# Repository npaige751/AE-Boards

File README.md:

Circuit board designs for acoustic imager.

Central hub board with an FPGA, connecting to four large boards surrounding it that hold the microphone array.

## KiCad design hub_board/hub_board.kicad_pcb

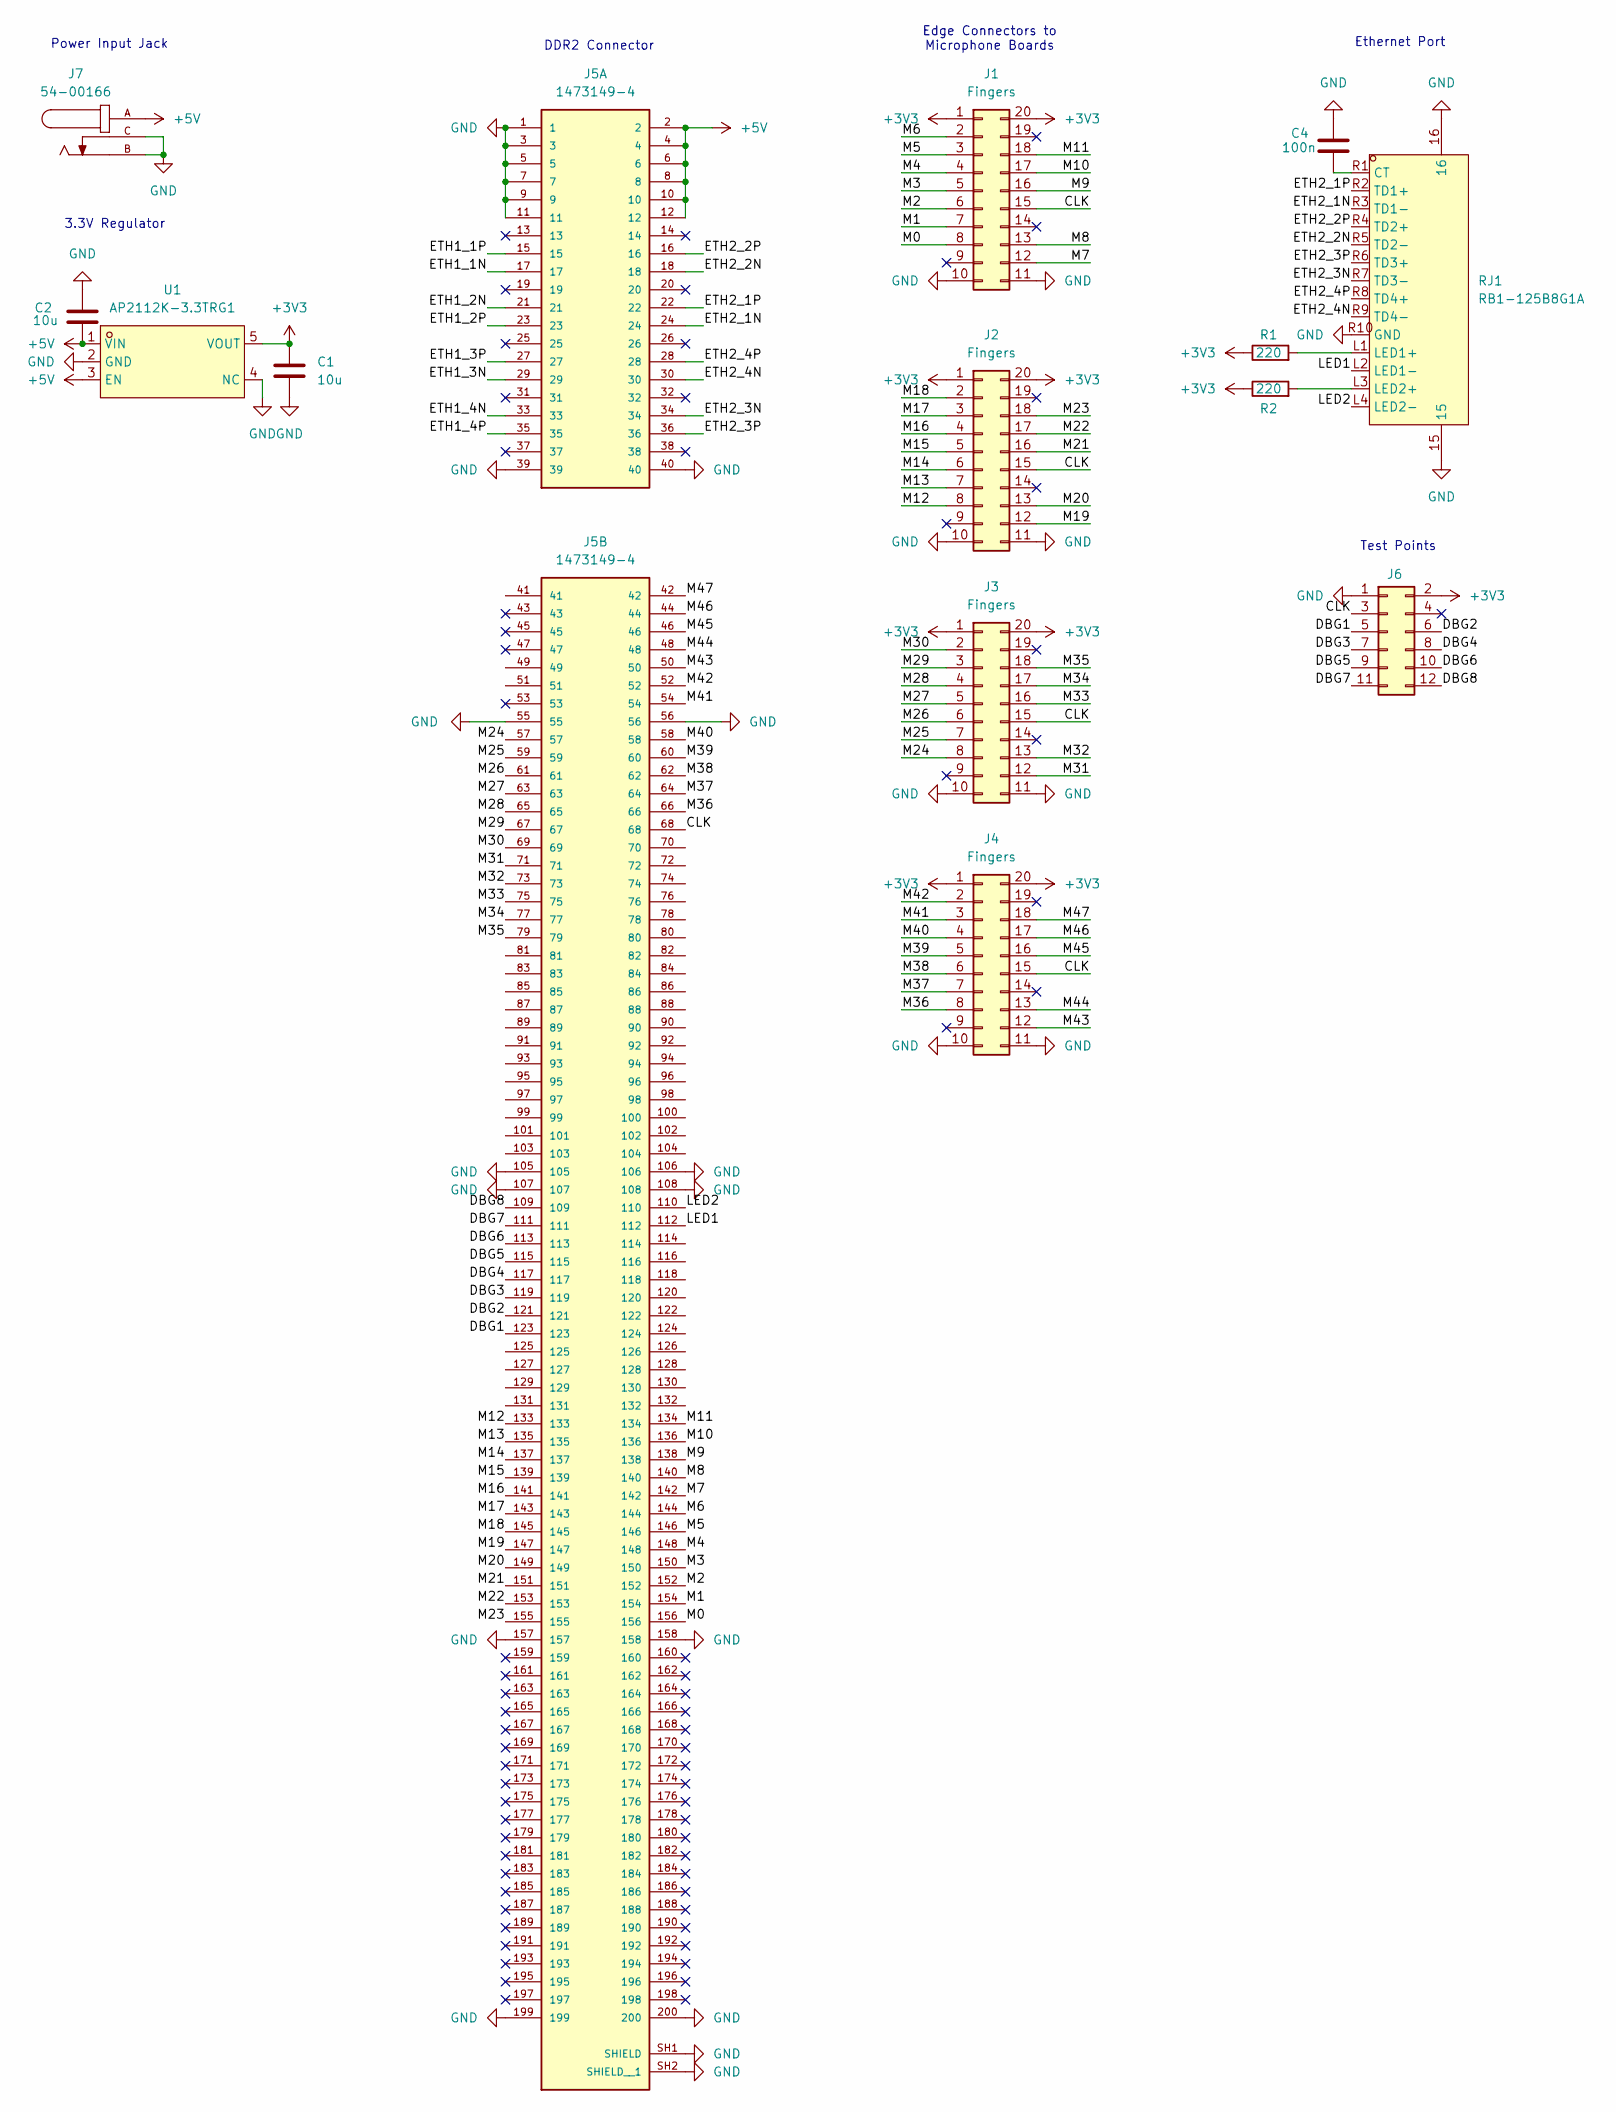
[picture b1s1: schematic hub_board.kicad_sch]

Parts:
C1, C2: 10u
C4: 100n
J1, J2, J3, J4: Fingers
J5: 1473149-4; TE_1473149-4
J6: Test Points
J7: 54-00166; TENSILITY_54-00166; PARTREV A
R1, R2: 220
RJ1: RB1-125B8G1A; RJ45-TH_RB1-125B8G1A; LCSC Part C363353
U1: AP2112K-3.3TRG1; SOT-25-5_L2.9-W1.6-P0.95-LS2.8-BL; LCSC Part C51118

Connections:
+3V3: C1.1, J1.1, J1.20, J2.1, J2.20, J3.1, J3.20, J4.1, J4.20, J6.2, R1.1, R2.1, U1.5 (VOUT)
+5V: C2.2, J5.2, J5.4, J5.6, J5.8, J5.10, J5.12, J7.A, U1.1 (VIN), U1.3 (EN)
/CLK: J1.15, J2.15, J3.15, J4.15, J5.68, J6.3
/DBG1: J5.123, J6.5
/DBG2: J5.121, J6.6
/DBG3: J5.119, J6.7
/DBG4: J5.117, J6.8
/DBG5: J5.115, J6.9
/DBG6: J5.113, J6.10
/DBG7: J5.111, J6.11
/DBG8: J5.109, J6.12
/ETH1_1N: J5.17
/ETH1_1P: J5.15
/ETH1_2N: J5.21
/ETH1_2P: J5.23
/ETH1_3N: J5.29
/ETH1_3P: J5.27
/ETH1_4N: J5.33
/ETH1_4P: J5.35
/ETH2_1N: J5.24, RJ1.R3 (TD1-)
/ETH2_1P: J5.22, RJ1.R2 (TD1+)
/ETH2_2N: J5.18, RJ1.R5 (TD2-)
/ETH2_2P: J5.16, RJ1.R4 (TD2+)
/ETH2_3N: J5.34, RJ1.R7 (TD3-)
/ETH2_3P: J5.36, RJ1.R6 (TD3+)
/ETH2_4N: J5.30, RJ1.R9 (TD4-)
/ETH2_4P: J5.28, RJ1.R8 (TD4+)
/LED1: J5.112, RJ1.L2 (LED1-)
/LED2: J5.110, RJ1.L4 (LED2-)
/M0: J1.8, J5.156
/M1: J1.7, J5.154
/M2: J1.6, J5.152
/M3: J1.5, J5.150
/M4: J1.4, J5.148
/M5: J1.3, J5.146
/M6: J1.2, J5.144
/M7: J1.12, J5.142
/M8: J1.13, J5.140
/M9: J1.16, J5.138
/M10: J1.17, J5.136
/M11: J1.18, J5.134
/M12: J2.8, J5.133
/M13: J2.7, J5.135
/M14: J2.6, J5.137
/M15: J2.5, J5.139
/M16: J2.4, J5.141
/M17: J2.3, J5.143
/M18: J2.2, J5.145
/M19: J2.12, J5.147
/M20: J2.13, J5.149
/M21: J2.16, J5.151
/M22: J2.17, J5.153
/M23: J2.18, J5.155
/M24: J3.8, J5.57
/M25: J3.7, J5.59
/M26: J3.6, J5.61
/M27: J3.5, J5.63
/M28: J3.4, J5.65
/M29: J3.3, J5.67
/M30: J3.2, J5.69
/M31: J3.12, J5.71
/M32: J3.13, J5.73
/M33: J3.16, J5.75
/M34: J3.17, J5.77
/M35: J3.18, J5.79
/M36: J4.8, J5.66
/M37: J4.7, J5.64
/M38: J4.6, J5.62
/M39: J4.5, J5.60
/M40: J4.4, J5.58
/M41: J4.3, J5.54
/M42: J4.2, J5.52
/M43: J4.12, J5.50
/M44: J4.13, J5.48
/M45: J4.16, J5.46
/M46: J4.17, J5.44
/M47: J4.18, J5.42
GND: C1.2, C2.1, C4.2, J1.10, J1.11, J2.10, J2.11, J3.10, J3.11, J4.10, J4.11, J5.1, J5.3, J5.5, J5.7, J5.9, J5.11, J5.39, J5.40, J5.55, J5.56, J5.105, J5.106, J5.107, J5.108, J5.157, J5.158, J5.199, J5.200, J5.SH1 (SHIELD), J5.SH2 (SHIELD__1), J6.1, J7.B, J7.C, RJ1.15, RJ1.16, RJ1.R10 (GND), U1.2 (GND), U1.4 (NC)
unnamed: C4.1, RJ1.R1 (CT)
unnamed: R1.2, RJ1.L1 (LED1+)
unnamed: R2.2, RJ1.L3 (LED2+)

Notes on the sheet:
3.3V Regulator
Power Input Jack
DDR2 Connector
Ethernet Port
Test Points
Edge Connectors to Microphone Boards

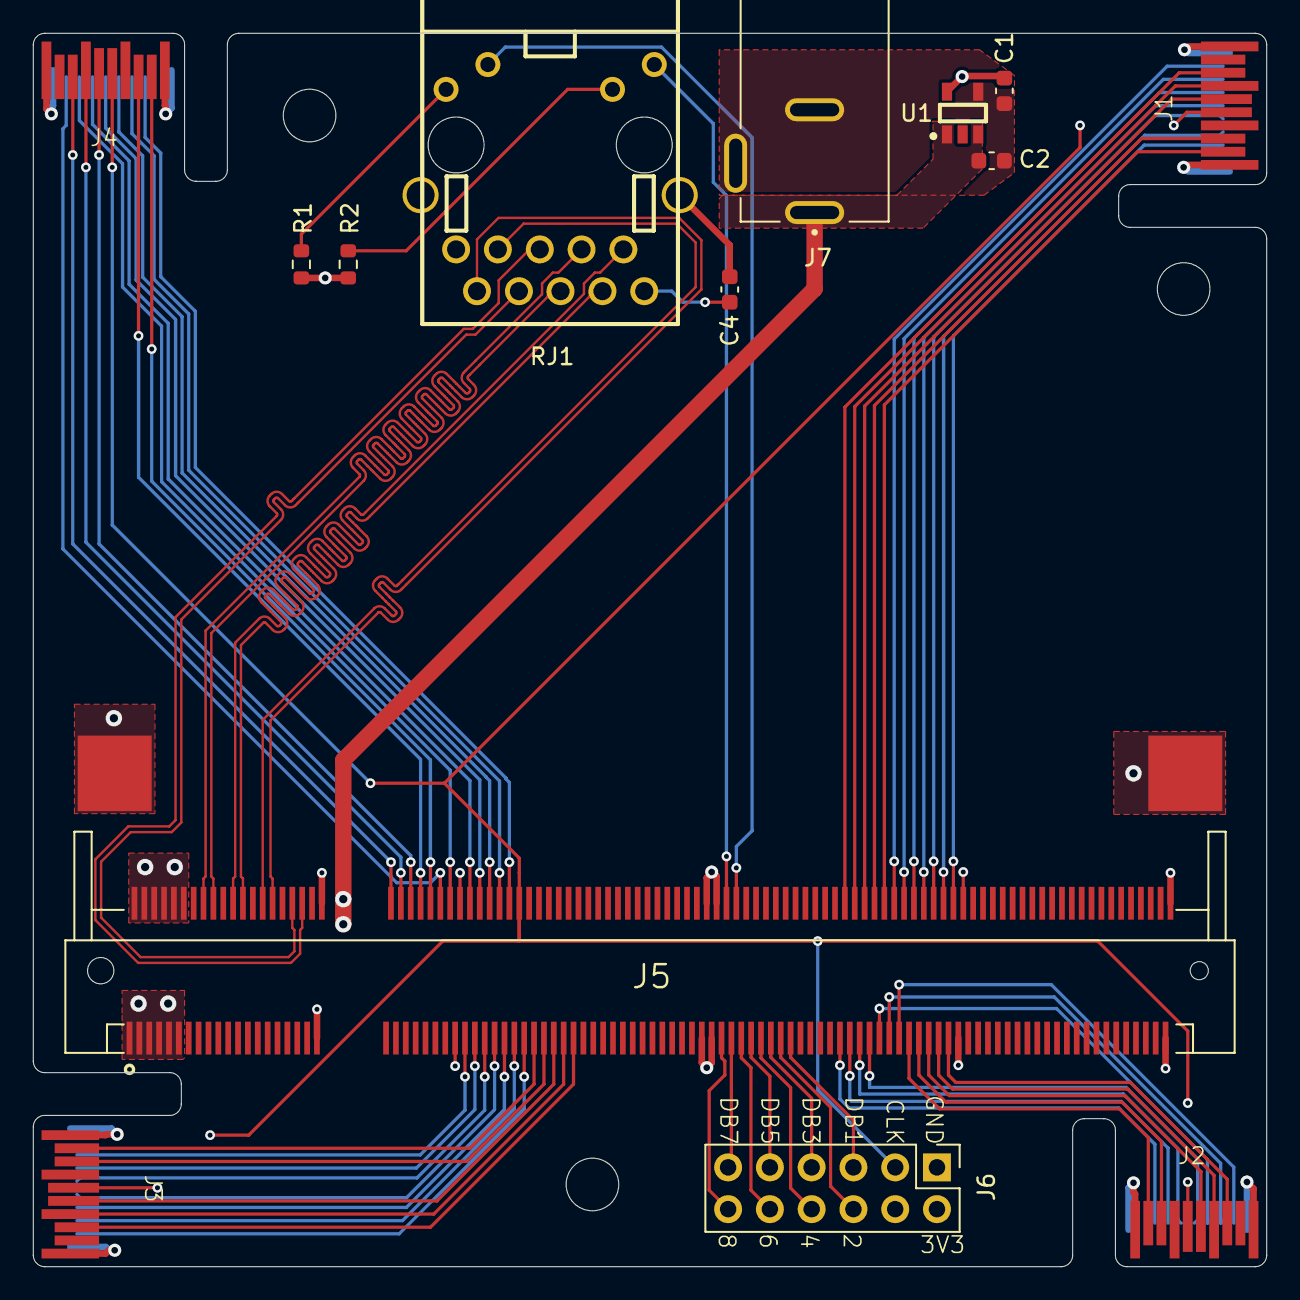
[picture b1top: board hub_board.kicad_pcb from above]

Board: 4 copper layers, 75.0 x 75.0 mm, 14 parts (0 on the bottom side), 73 nets.

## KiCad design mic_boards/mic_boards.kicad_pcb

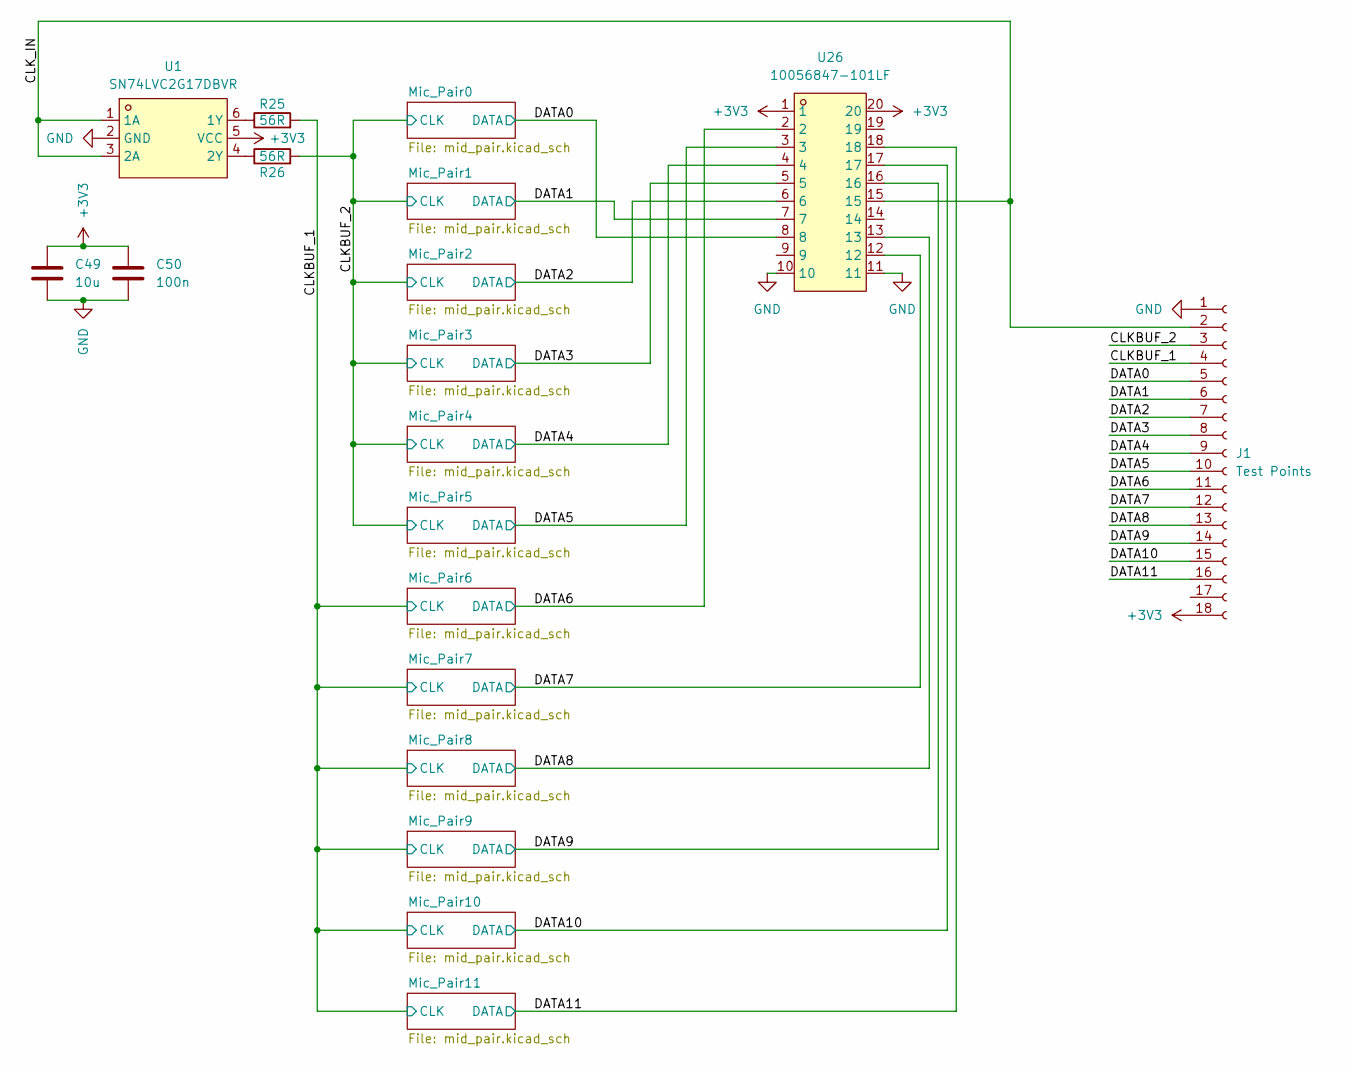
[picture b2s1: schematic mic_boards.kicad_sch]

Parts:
C49: 10u
C50: 100n
J1: Test Points
R25, R26: 56R
U1: SN74LVC2G17DBVR; SOT-23-6_L2.9-W1.6-P0.95-LS2.8-BL; LCSC Part C10429
U26: 10056847-101LF; CONN-SMD_20P-L11.0-W7.38-P0.80; LCSC Part C5070484

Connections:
+3V3: C49.1, C50.1, J1.18, U1.5 (VCC), U26.1, U26.20; also elsewhere on the board
/CLKBUF_1: J1.4, R25.2; also elsewhere on the board
/CLKBUF_2: J1.3, R26.2; also elsewhere on the board
/CLK_IN: J1.2, U1.1 (1A), U1.3 (2A), U26.15
/DATA0: J1.5, U26.8; also elsewhere on the board
/DATA1: J1.6, U26.7; also elsewhere on the board
/DATA2: J1.7, U26.6; also elsewhere on the board
/DATA3: J1.8, U26.5; also elsewhere on the board
/DATA4: J1.9, U26.4; also elsewhere on the board
/DATA5: J1.10, U26.3; also elsewhere on the board
/DATA6: J1.11, U26.2; also elsewhere on the board
/DATA7: J1.12, U26.12; also elsewhere on the board
/DATA8: J1.13, U26.13; also elsewhere on the board
/DATA9: J1.14, U26.16; also elsewhere on the board
/DATA10: J1.15, U26.17; also elsewhere on the board
/DATA11: J1.16, U26.18; also elsewhere on the board
GND: C49.2, C50.2, J1.1, U1.2 (GND), U26.10, U26.11; also elsewhere on the board
unnamed: R25.1, U1.6 (1Y)
unnamed: R26.1, U1.4 (2Y)

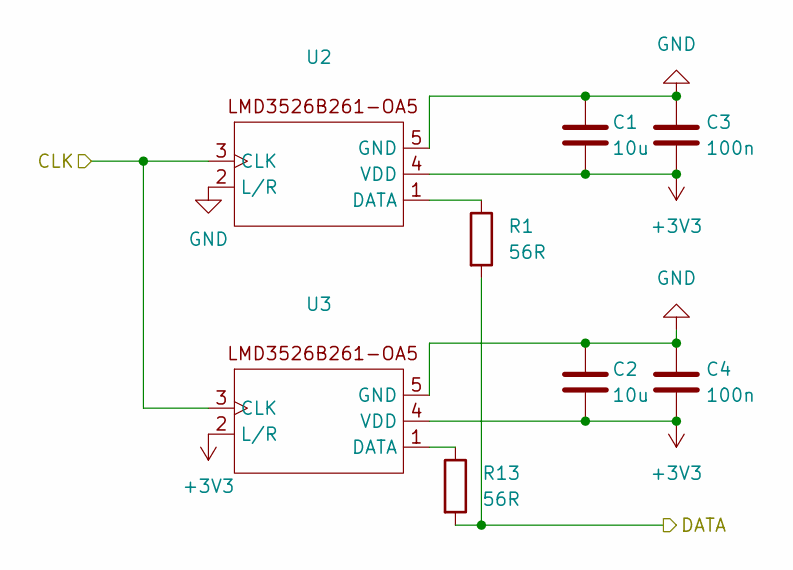
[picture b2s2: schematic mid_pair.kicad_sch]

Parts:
C1, C2: 10u
C3, C4: 100n
R1, R13: 56R
U2, U3: (no value)

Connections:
+3V3: C1.2, C2.2, C3.2, C4.2, U2.4 (VDD), U3.2 (L/R), U3.4 (VDD); also elsewhere on the board
/CLKBUF_2: U2.3 (CLK), U3.3 (CLK); also elsewhere on the board
/DATA0: R1.2, R13.2; also elsewhere on the board
GND: C1.1, C2.1, C3.1, C4.1, U2.2 (L/R), U2.5 (GND), U3.5 (GND); also elsewhere on the board
unnamed: R1.1, U2.1 (DATA)
unnamed: R13.1, U3.1 (DATA)

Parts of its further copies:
C5, C6, C9, C10, C13, C14, C17, C18, C21, C22, C25, C26, C29, C30, C33, C34, C37, C38, C41, C42, C45, C46: 10u
C7, C8, C11, C12, C15, C16, C19, C20, C23, C24, C27, C28, C31, C32, C35, C36, C39, C40, C43, C44, C47, C48: 100n
R2, R3, R4, R5, R6, R7, R8, R9, R10, R11, R12, R14, R15, R16, R17, R18, R19, R20, R21, R22, R23, R24: 56R
U4, U5, U6, U7, U8, U9, U10, U11, U12, U13, U14, U15, U16, U17, U18, U19, U20, U21, U22, U23, U24, U25: (no value)

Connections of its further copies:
+3V3: C5.2, C6.2, C7.2, C8.2, C9.2, C10.2, C11.2, C12.2, C13.2, C14.2, C15.2, C16.2, C17.2, C18.2, C19.2, C20.2, C21.2, C22.2, C23.2, C24.2, C25.2, C26.2, C27.2, C28.2, C29.2, C30.2, C31.2, C32.2, C33.2, C34.2, C35.2, C36.2, C37.2, C38.2, C39.2, C40.2, C41.2, C42.2, C43.2, C44.2, C45.2, C46.2, C47.2, C48.2, U4.4 (VDD), U5.2 (L/R), U5.4 (VDD), U6.4 (VDD), U7.2 (L/R), U7.4 (VDD), U8.4 (VDD), U9.2 (L/R), U9.4 (VDD), U10.4 (VDD), U11.2 (L/R), U11.4 (VDD), U12.4 (VDD), U13.2 (L/R), U13.4 (VDD), U14.4 (VDD), U15.2 (L/R), U15.4 (VDD), U16.4 (VDD), U17.2 (L/R), U17.4 (VDD), U18.4 (VDD), U19.2 (L/R), U19.4 (VDD), U20.4 (VDD), U21.2 (L/R), U21.4 (VDD), U22.4 (VDD), U23.2 (L/R), U23.4 (VDD), U24.4 (VDD), U25.2 (L/R), U25.4 (VDD); also elsewhere on the board
/CLKBUF_1: U14.3 (CLK), U15.3 (CLK), U16.3 (CLK), U17.3 (CLK), U18.3 (CLK), U19.3 (CLK), U20.3 (CLK), U21.3 (CLK), U22.3 (CLK), U23.3 (CLK), U24.3 (CLK), U25.3 (CLK); also elsewhere on the board
/CLKBUF_2: U4.3 (CLK), U5.3 (CLK), U6.3 (CLK), U7.3 (CLK), U8.3 (CLK), U9.3 (CLK), U10.3 (CLK), U11.3 (CLK), U12.3 (CLK), U13.3 (CLK); also elsewhere on the board
/DATA1: R2.2, R14.2; also elsewhere on the board
/DATA2: R3.2, R15.2; also elsewhere on the board
/DATA3: R4.2, R16.2; also elsewhere on the board
/DATA4: R5.2, R17.2; also elsewhere on the board
/DATA5: R6.2, R18.2; also elsewhere on the board
/DATA6: R7.2, R19.2; also elsewhere on the board
/DATA7: R8.2, R20.2; also elsewhere on the board
/DATA8: R9.2, R21.2; also elsewhere on the board
/DATA9: R10.2, R22.2; also elsewhere on the board
/DATA10: R11.2, R23.2; also elsewhere on the board
/DATA11: R12.2, R24.2; also elsewhere on the board
GND: C5.1, C6.1, C7.1, C8.1, C9.1, C10.1, C11.1, C12.1, C13.1, C14.1, C15.1, C16.1, C17.1, C18.1, C19.1, C20.1, C21.1, C22.1, C23.1, C24.1, C25.1, C26.1, C27.1, C28.1, C29.1, C30.1, C31.1, C32.1, C33.1, C34.1, C35.1, C36.1, C37.1, C38.1, C39.1, C40.1, C41.1, C42.1, C43.1, C44.1, C45.1, C46.1, C47.1, C48.1, U4.2 (L/R), U4.5 (GND), U5.5 (GND), U6.2 (L/R), U6.5 (GND), U7.5 (GND), U8.2 (L/R), U8.5 (GND), U9.5 (GND), U10.2 (L/R), U10.5 (GND), U11.5 (GND), U12.2 (L/R), U12.5 (GND), U13.5 (GND), U14.2 (L/R), U14.5 (GND), U15.5 (GND), U16.2 (L/R), U16.5 (GND), U17.5 (GND), U18.2 (L/R), U18.5 (GND), U19.5 (GND), U20.2 (L/R), U20.5 (GND), U21.5 (GND), U22.2 (L/R), U22.5 (GND), U23.5 (GND), U24.2 (L/R), U24.5 (GND), U25.5 (GND); also elsewhere on the board
unnamed: R2.1, U4.1 (DATA)
unnamed: R14.1, U5.1 (DATA)
unnamed: R3.1, U6.1 (DATA)
unnamed: R15.1, U7.1 (DATA)
unnamed: R4.1, U8.1 (DATA)
unnamed: R16.1, U9.1 (DATA)
unnamed: R5.1, U10.1 (DATA)
unnamed: R17.1, U11.1 (DATA)
unnamed: R6.1, U12.1 (DATA)
unnamed: R18.1, U13.1 (DATA)
unnamed: R7.1, U14.1 (DATA)
unnamed: R19.1, U15.1 (DATA)
unnamed: R8.1, U16.1 (DATA)
unnamed: R20.1, U17.1 (DATA)
unnamed: R9.1, U18.1 (DATA)
unnamed: R21.1, U19.1 (DATA)
unnamed: R10.1, U20.1 (DATA)
unnamed: R22.1, U21.1 (DATA)
unnamed: R11.1, U22.1 (DATA)
unnamed: R23.1, U23.1 (DATA)
unnamed: R12.1, U24.1 (DATA)
unnamed: R24.1, U25.1 (DATA)

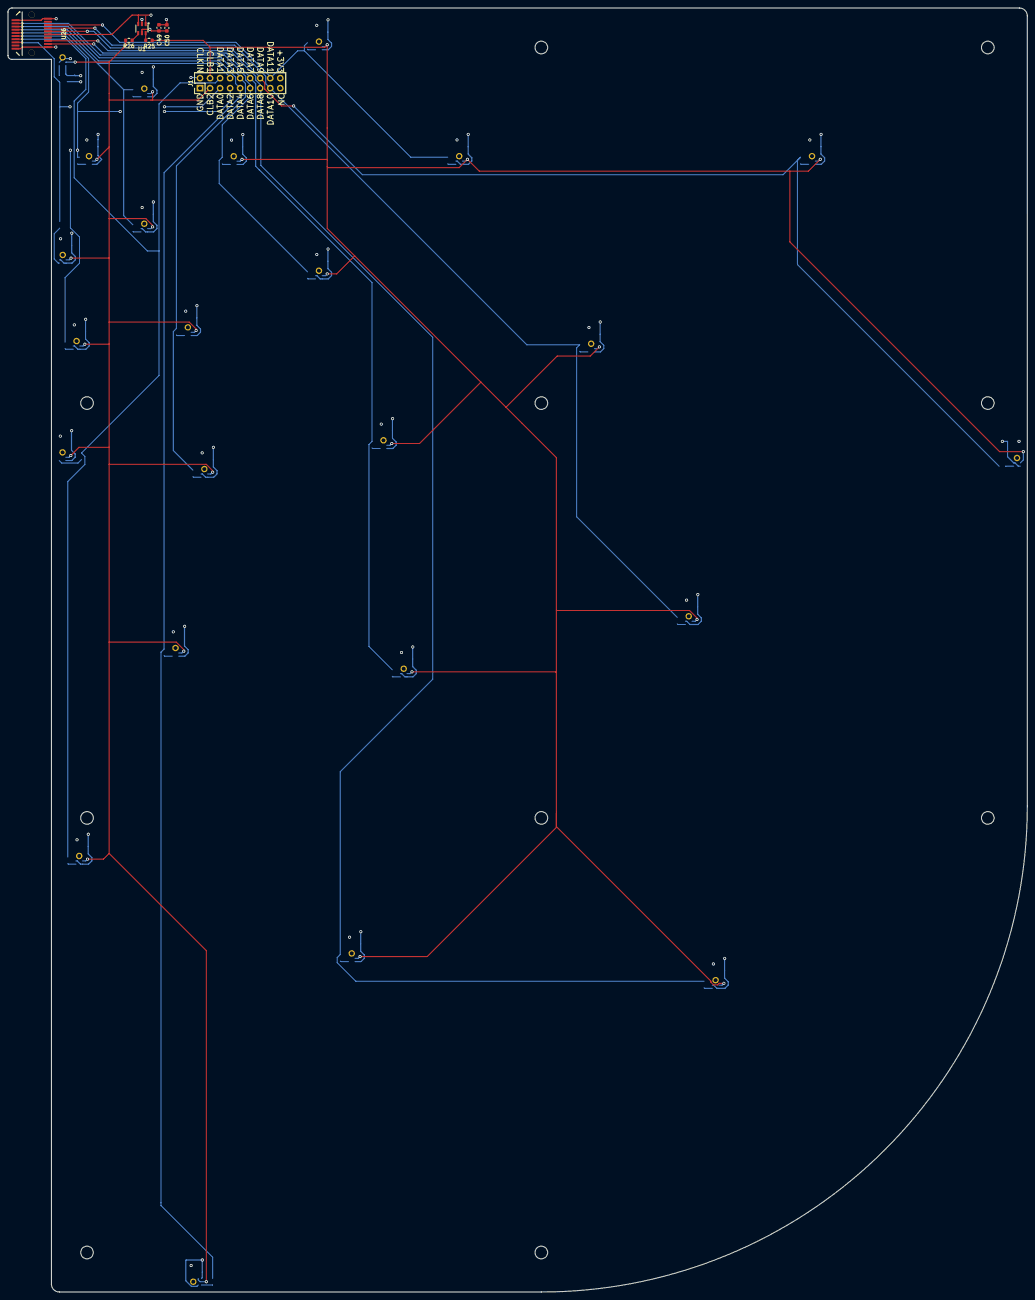
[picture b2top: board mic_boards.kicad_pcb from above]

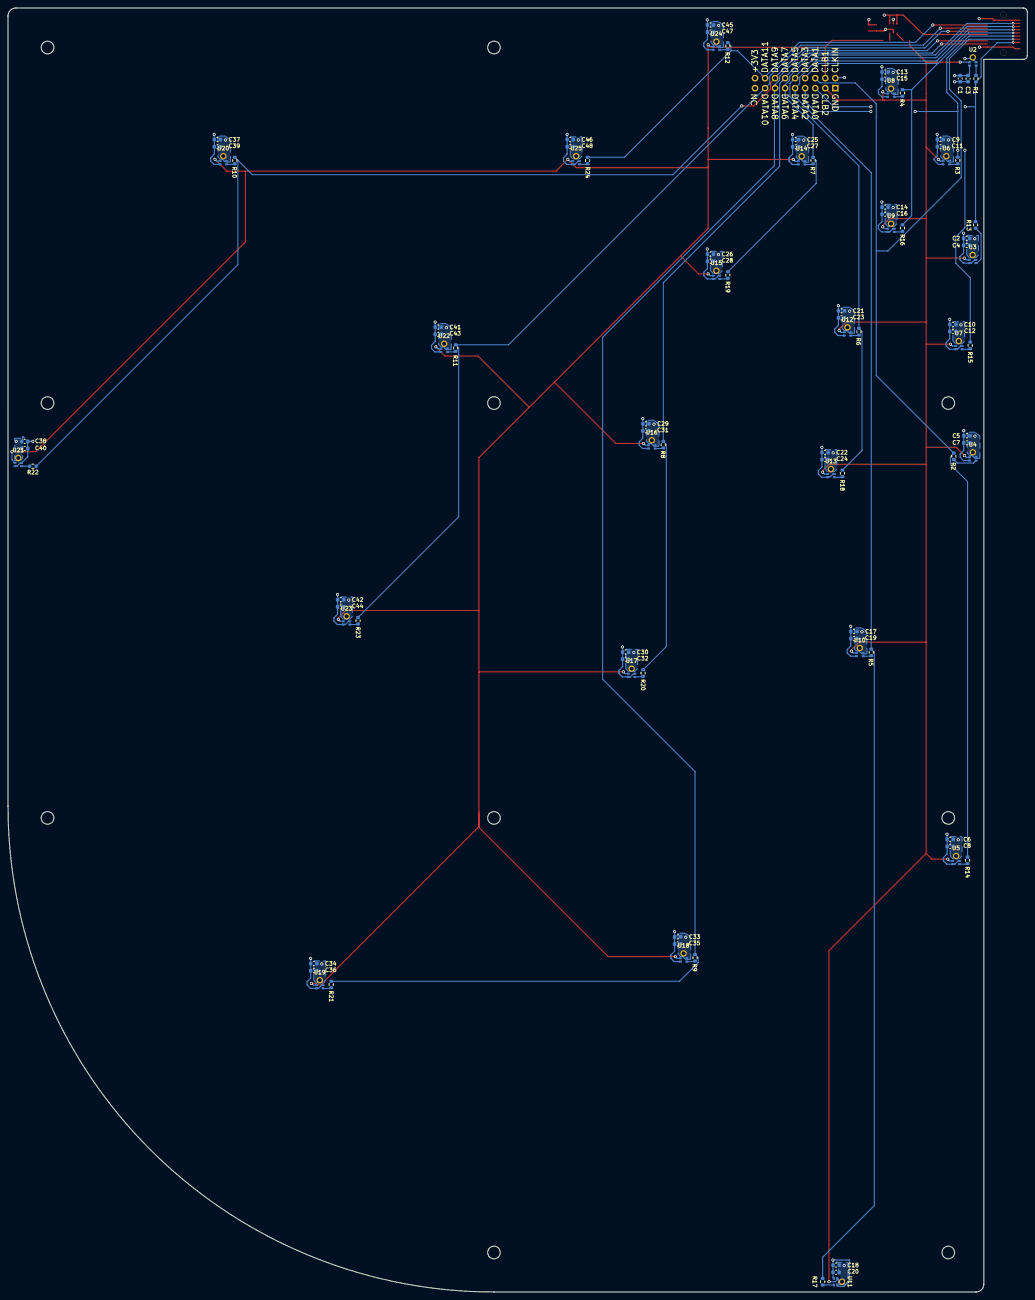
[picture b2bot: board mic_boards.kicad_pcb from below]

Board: 4 copper layers, 258.0 x 325.0 mm, 103 parts (96 on the bottom side), 43 nets.

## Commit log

2025-07-22 Microphone boards; WIP hub board
2025-07-22 Add license and readme
2025-07-22 Finish hub board layout
2025-07-23 Fix DDR2 connector position & reroute; add test points
2025-07-25 Flip Ethernet port to front side
2025-08-01 Redo layout (wip)
2025-08-01 Flip ethernet port & fix routing
2025-08-01 Finish routing hub board
2025-08-01 Fix solder mask gap size on DDR connector
